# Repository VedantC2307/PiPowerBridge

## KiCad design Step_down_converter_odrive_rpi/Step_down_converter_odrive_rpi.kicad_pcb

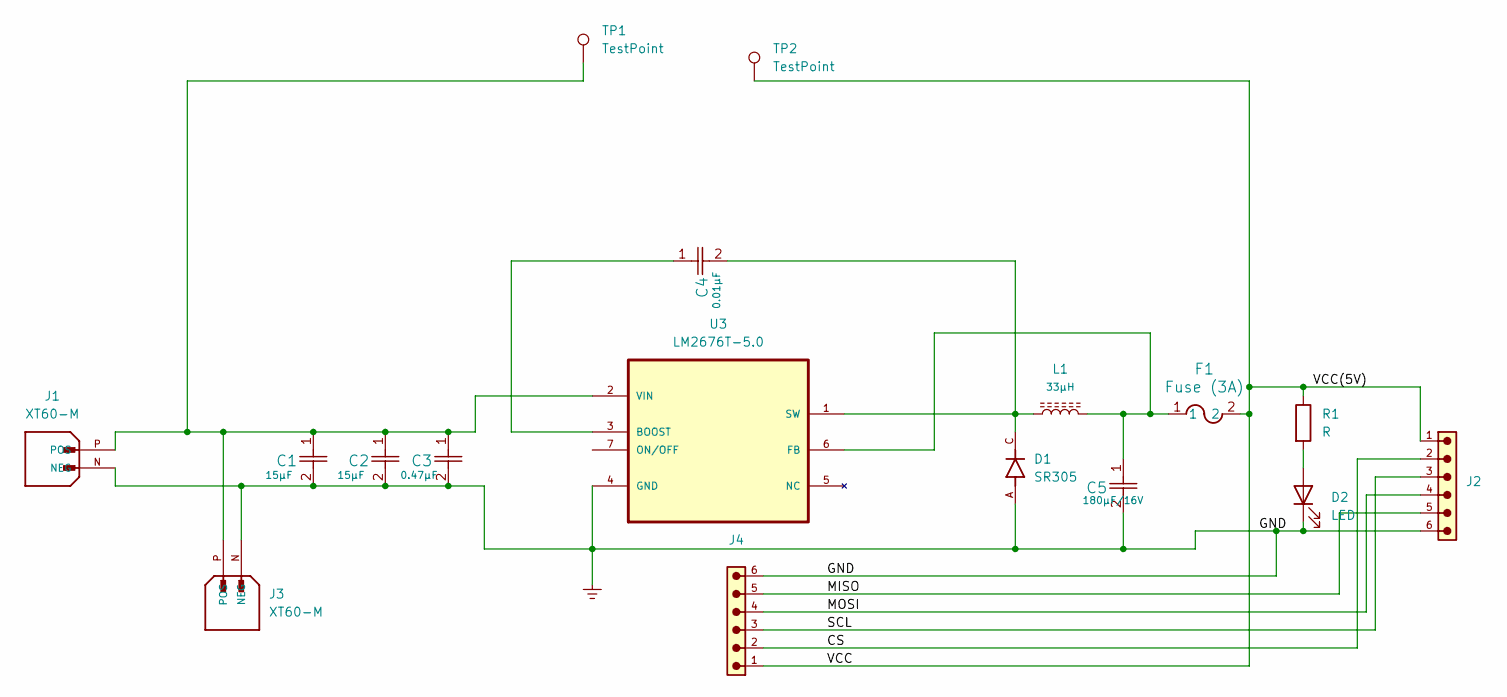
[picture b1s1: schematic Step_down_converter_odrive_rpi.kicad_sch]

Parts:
C1, C2: 15µF; PCB capacitor 15uF
C3: 0.47µF; CAPRR254W54L381T254H466
C4: 0.01µF; CAP_C410C_AX_Z5U_U5TA_KEM
C5: 180µF/16V; CAPPRD350W60D800H1200
D1: SR305; DIOAD1990W125L900D530; PARTREV K2105
D2: LED; LED_D2.0mm_W4.0mm_H2.8mm_FlatTop
F1: Fuse (3A); FUSE_CMF-RL50A-0_BRN
J1, J3: XT60-M; AMASS_XT60-M; PARTREV V1.2
J2, J4: PinHeader_1x06_P2.54mm_Vertical; PART-NUMBER 61300611121
L1: 33µH; IND_SBC8-330-452_KEM
R1: R; R_Axial_DIN0204_L3.6mm_D1.6mm_P7.62mm_Horizontal
TP1, TP2: TestPoint; TestPoint_Loop_D2.50mm_Drill1.0mm_LowProfile
U3: LM2676T-5.0; TA07B; MPN LM2676T-5.0

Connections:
/CS: J2.2, J4.2
/MISO: J2.5, J4.5
/MOSI: J2.4, J4.4
/SCL: J2.3, J4.3
/VCC: F1.2, J2.1, J4.1, R1.1, TP2.1
GND_POWER: C1.2, C2.2, C3.2, C5.2, D1.A, D2.1 (K), J1.N (NEG), J2.6, J3.N (NEG), J4.6, U3.4 (GND)
unnamed: D2.2 (A), R1.2
unnamed: C1.1, C2.1, C3.1, J1.P (POS), J3.P (POS), TP1.1, U3.2 (VIN)
unnamed: C4.1, U3.3 (BOOST)
unnamed: C5.1, F1.1, L1.2, U3.6 (FB)
unnamed: C4.2, D1.C, L1.1, U3.1 (SW)

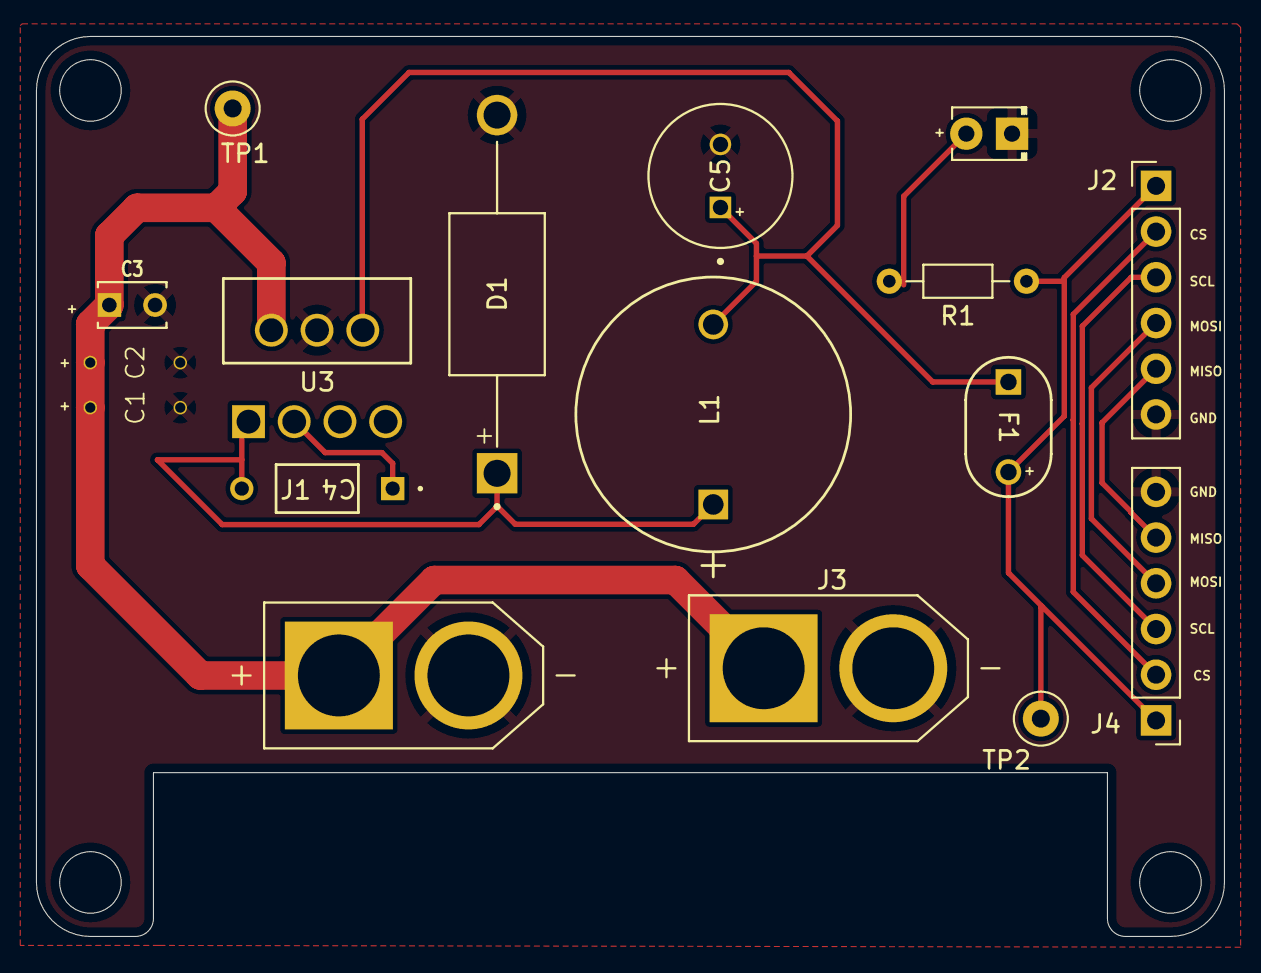
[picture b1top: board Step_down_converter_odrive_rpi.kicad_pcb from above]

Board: 2 copper layers, 66.0 x 50.0 mm, 17 parts (0 on the bottom side), 11 nets.
